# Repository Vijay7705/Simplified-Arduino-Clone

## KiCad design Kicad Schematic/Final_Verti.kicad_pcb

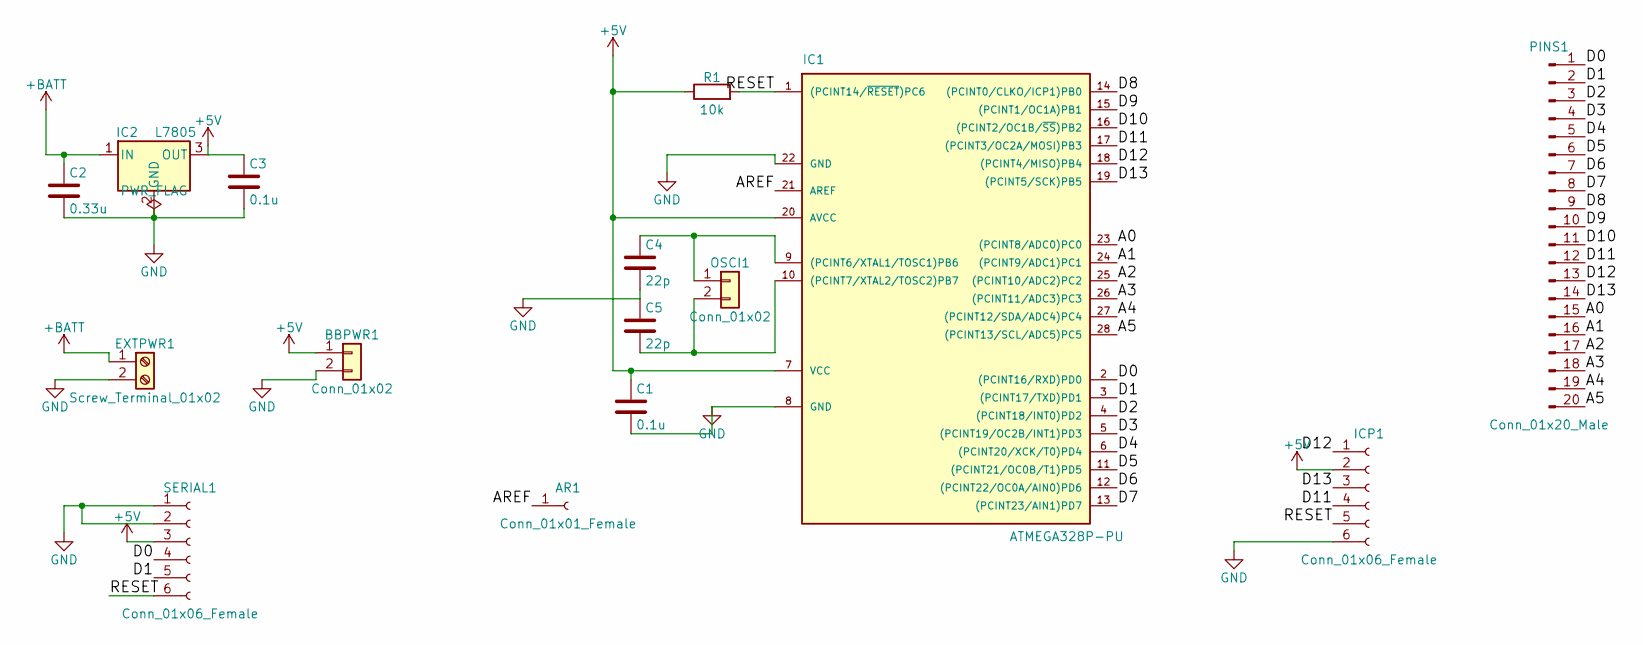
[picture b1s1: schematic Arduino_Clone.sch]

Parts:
AR1: Conn_01x01_Female; Pin_Header_Straight_1x01_Pitch2.54mm
BBPWR1: Conn_01x02; Pin_Header_Straight_1x02_Pitch2.54mm
C1, C3: 0.1u; C_Rect_L7.0mm_W6.5mm_P5.00mm
C2: 0.33u; C_Rect_L7.0mm_W6.5mm_P5.00mm
C4, C5: 22p; C_Disc_D4.7mm_W2.5mm_P5.00mm
EXTPWR1: Screw_Terminal_01x02; TerminalBlock_Altech_AK300-2_P5.00mm
IC1: ATMEGA328P-PU; DIP-28_W7.62mm
IC2: L7805; TO-220-3_Vertical
ICP1: Conn_01x06_Female; Pin_Header_Straight_1x06_Pitch2.54mm
OSCI1: Conn_01x02; Crystal_HC49-U_Vertical
PINS1: Conn_01x20_Male; Pin_Header_Straight_1x20_Pitch2.54mm
R1: 10k; R_Axial_DIN0207_L6.3mm_D2.5mm_P10.16mm_Horizontal
SERIAL1: Conn_01x06_Female; Pin_Header_Straight_1x06_Pitch2.54mm

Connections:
+5V: BBPWR1.1, C1.1, C3.1, IC1.7 (VCC), IC1.20 (AVCC), IC2.3 (OUT), ICP1.2, R1.1, SERIAL1.3
+BATT: C2.1, EXTPWR1.1, IC2.1 (IN)
/A0: IC1.23 ((PCINT8/ADC0)PC0), PINS1.15
/A1: IC1.24 ((PCINT9/ADC1)PC1), PINS1.16
/A2: IC1.25 ((PCINT10/ADC2)PC2), PINS1.17
/A3: IC1.26 ((PCINT11/ADC3)PC3), PINS1.18
/A4: IC1.27 ((PCINT12/SDA/ADC4)PC4), PINS1.19
/A5: IC1.28 ((PCINT13/SCL/ADC5)PC5), PINS1.20
/AREF: AR1.1, IC1.21 (AREF)
/D0: IC1.2 ((PCINT16/RXD)PD0), PINS1.1, SERIAL1.4
/D1: IC1.3 ((PCINT17/TXD)PD1), PINS1.2, SERIAL1.5
/D2: IC1.4 ((PCINT18/INT0)PD2), PINS1.3
/D3: IC1.5 ((PCINT19/OC2B/INT1)PD3), PINS1.4
/D4: IC1.6 ((PCINT20/XCK/T0)PD4), PINS1.5
/D5: IC1.11 ((PCINT21/OC0B/T1)PD5), PINS1.6
/D6: IC1.12 ((PCINT22/OC0A/AIN0)PD6), PINS1.7
/D7: IC1.13 ((PCINT23/AIN1)PD7), PINS1.8
/D8: IC1.14 ((PCINT0/CLKO/ICP1)PB0), PINS1.9
/D9: IC1.15 ((PCINT1/OC1A)PB1), PINS1.10
/D10: IC1.16 ((PCINT2/OC1B/~SS~)PB2), PINS1.11
/D11: IC1.17 ((PCINT3/OC2A/MOSI)PB3), ICP1.4, PINS1.12
/D12: IC1.18 ((PCINT4/MISO)PB4), ICP1.1, PINS1.13
/D13: IC1.19 ((PCINT5/SCK)PB5), ICP1.3, PINS1.14
/RESET: IC1.1 ((PCINT14/~RESET~)PC6), ICP1.5, R1.2, SERIAL1.6
GND: BBPWR1.2, C1.2, C2.2, C3.2, C4.2, C5.1, EXTPWR1.2, IC1.8 (GND), IC1.22 (GND), IC2.2 (GND), ICP1.6, SERIAL1.1, SERIAL1.2
unnamed: C4.1, IC1.9 ((PCINT6/XTAL1/TOSC1)PB6), OSCI1.1
unnamed: C5.2, IC1.10 ((PCINT7/XTAL2/TOSC2)PB7), OSCI1.2

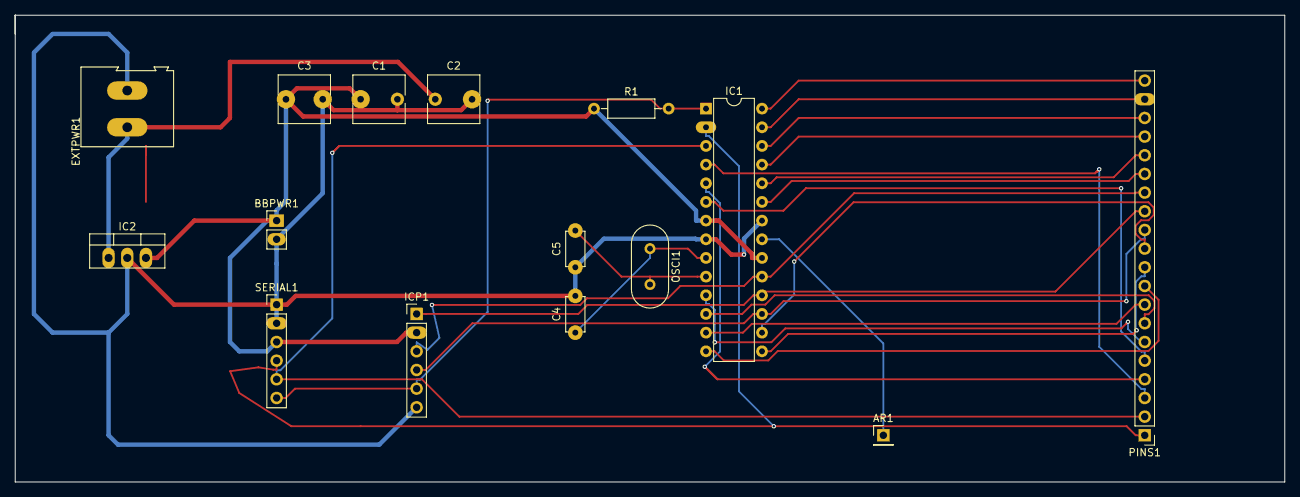
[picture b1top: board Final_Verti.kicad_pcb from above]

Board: 2 copper layers, 172.7 x 63.5 mm, 15 parts (0 on the bottom side), 27 nets.
